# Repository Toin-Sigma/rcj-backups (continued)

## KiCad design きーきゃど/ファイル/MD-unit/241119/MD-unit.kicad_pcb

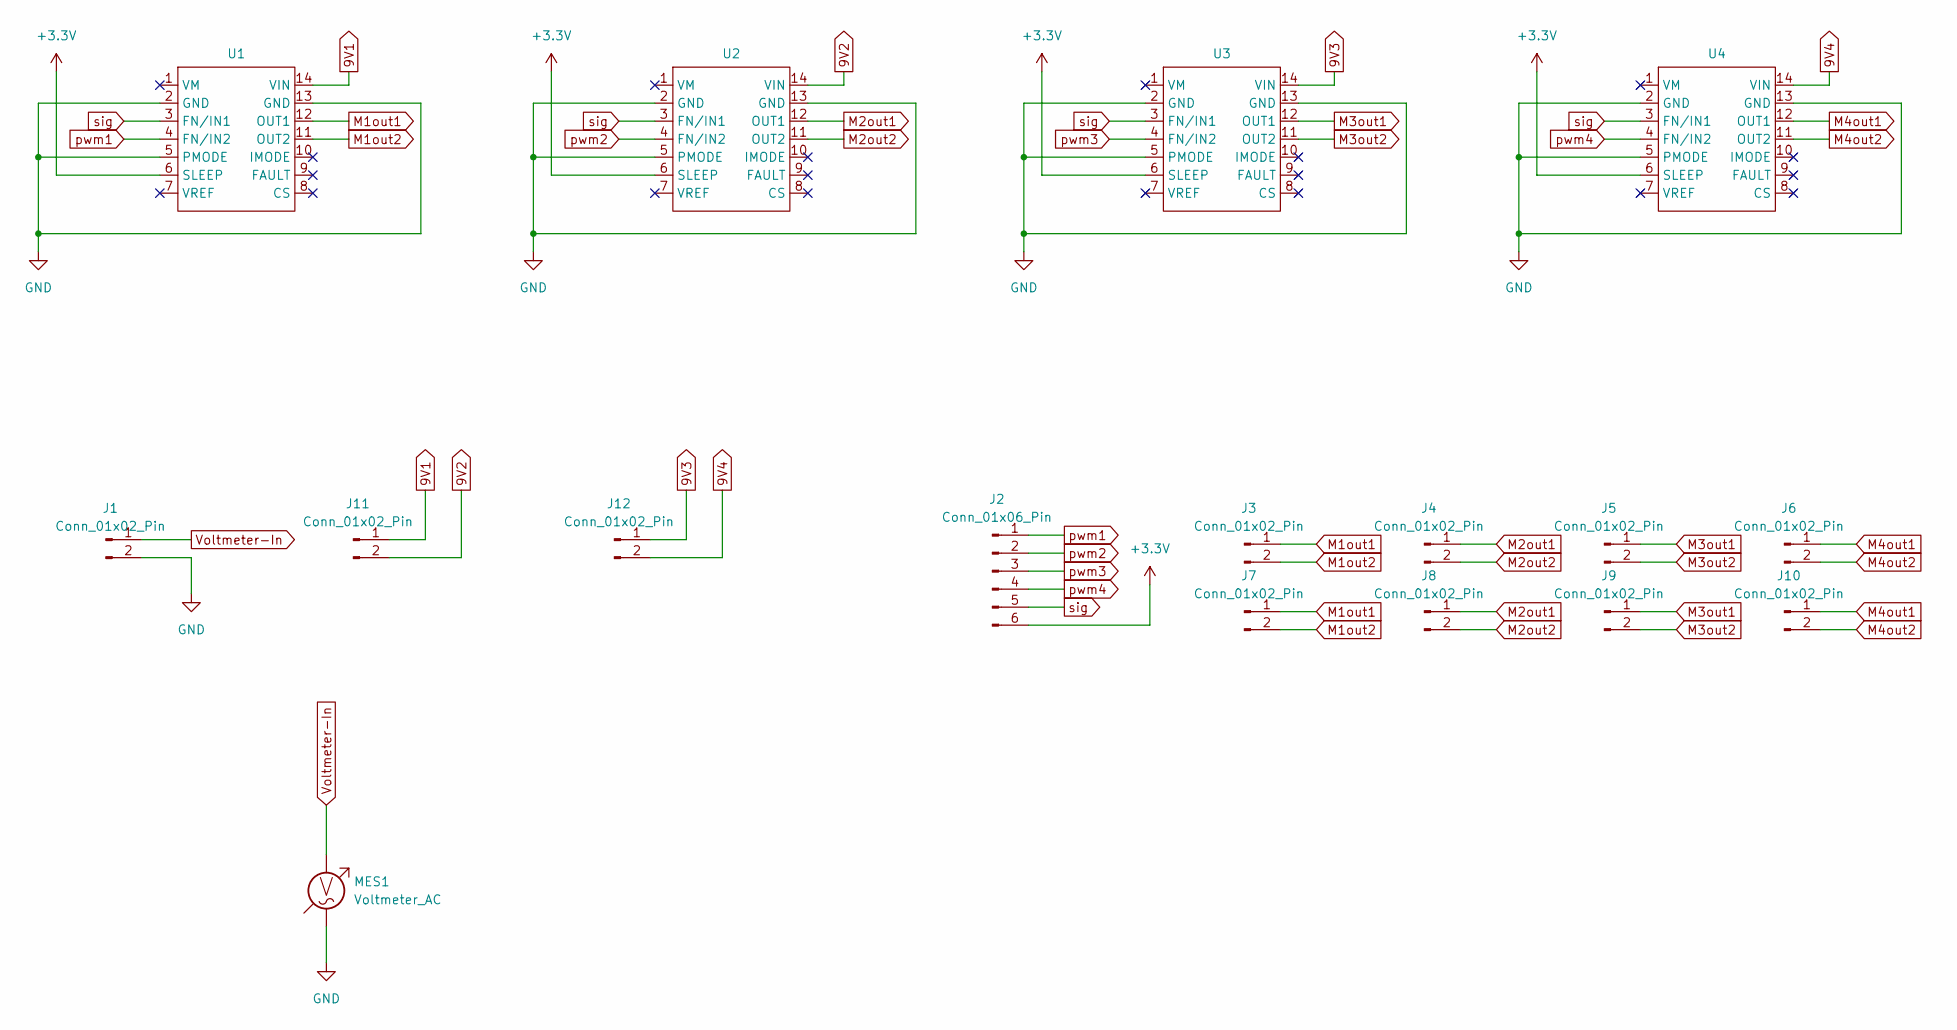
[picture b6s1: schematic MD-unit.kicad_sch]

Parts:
J1, J3, J4, J5, J6, J11, J12: Conn_01x02_Pin; AMASS_XT30U-M_1x02_P5.0mm_Vertical
J2: Conn_01x06_Pin; JST_XH_B6B-XH-A_1x06_P2.50mm_Vertical
J7, J8, J9, J10: Conn_01x02_Pin; JST_XH_B2B-XH-A_1x02_P2.50mm_Vertical
MES1: Voltmeter_AC; VoltMeter
U1, U2, U3, U4: DRV8874

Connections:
9V1: J11.1, U1.14 (VIN)
9V2: J11.2, U2.14 (VIN)
9V3: J12.1, U3.14 (VIN)
9V4: J12.2, U4.14 (VIN)
+3.3V: J2.6, U1.6 (SLEEP), U2.6 (SLEEP), U3.6 (SLEEP), U4.6 (SLEEP)
GND: J1.2, MES1.1, U1.2 (GND), U1.5 (PMODE), U1.13 (GND), U2.2 (GND), U2.5 (PMODE), U2.13 (GND), U3.2 (GND), U3.5 (PMODE), U3.13 (GND), U4.2 (GND), U4.5 (PMODE), U4.13 (GND)
M1out1: J3.1, J7.1, U1.12 (OUT1)
M1out2: J3.2, J7.2, U1.11 (OUT2)
M2out1: J4.1, J8.1, U2.12 (OUT1)
M2out2: J4.2, J8.2, U2.11 (OUT2)
M3out1: J5.1, J9.1, U3.12 (OUT1)
M3out2: J5.2, J9.2, U3.11 (OUT2)
M4out1: J6.1, J10.1, U4.12 (OUT1)
M4out2: J6.2, J10.2, U4.11 (OUT2)
Voltmeter-In: J1.1, MES1.2
pwm1: J2.1, U1.4 (FN/IN2)
pwm2: J2.2, U2.4 (FN/IN2)
pwm3: J2.3, U3.4 (FN/IN2)
pwm4: J2.4, U4.4 (FN/IN2)
sig: J2.5, U1.3 (FN/IN1), U2.3 (FN/IN1), U3.3 (FN/IN1), U4.3 (FN/IN1)

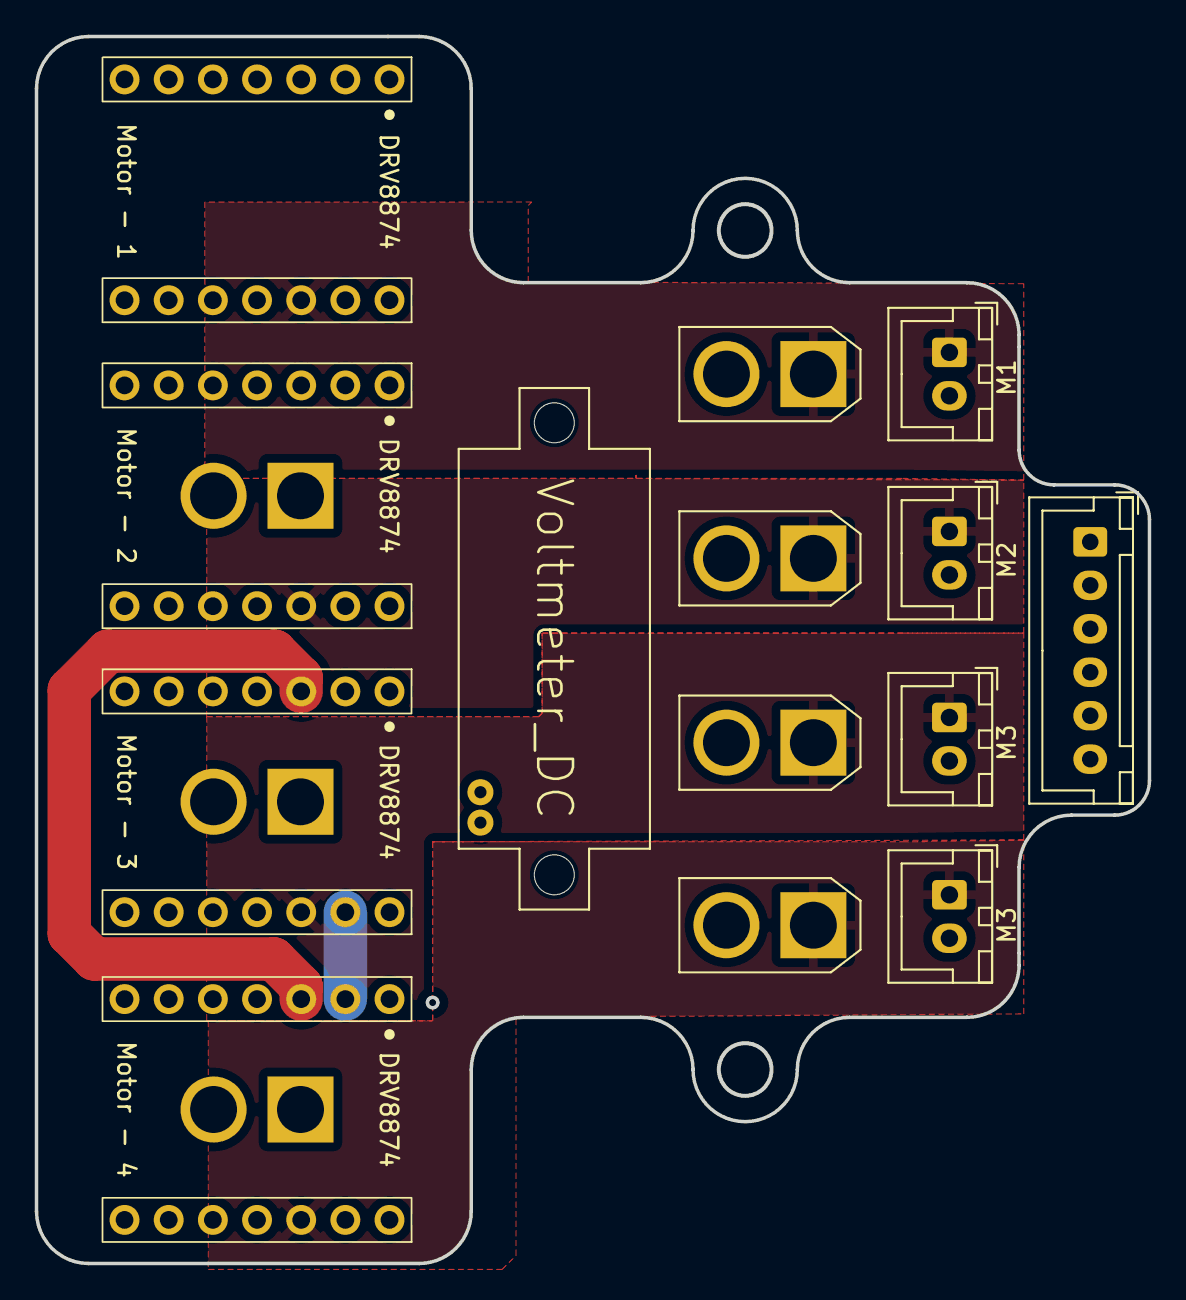
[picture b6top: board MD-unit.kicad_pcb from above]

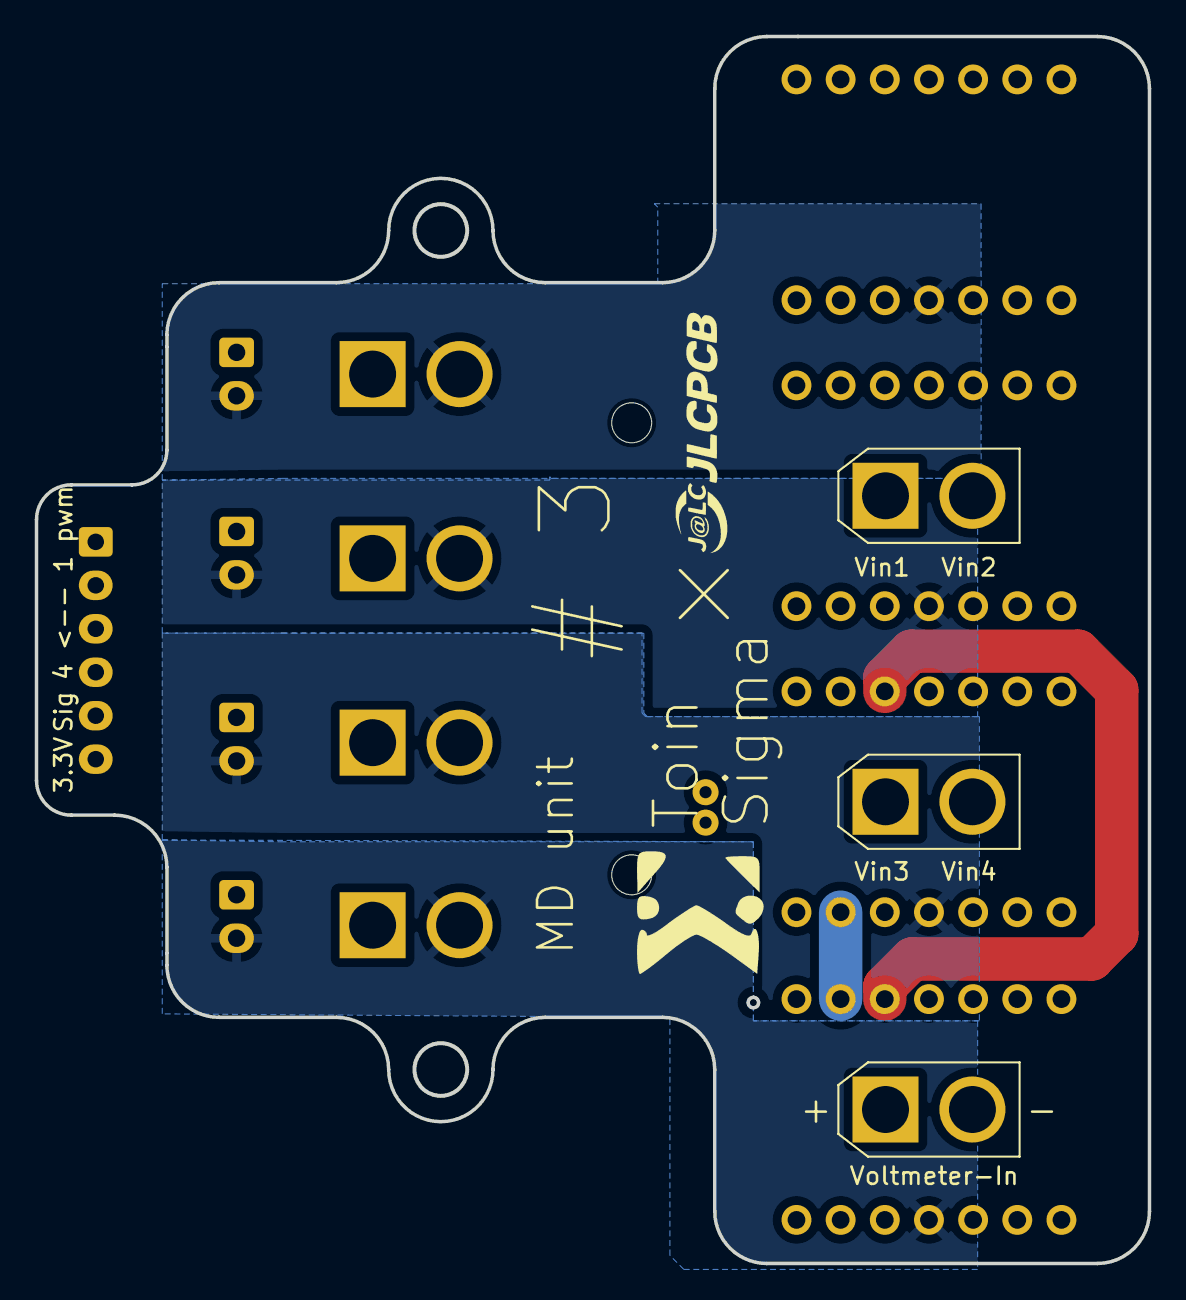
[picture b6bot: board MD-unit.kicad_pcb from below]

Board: 4 copper layers, 64.0 x 70.6 mm, 17 parts (3 on the bottom side), 20 nets.

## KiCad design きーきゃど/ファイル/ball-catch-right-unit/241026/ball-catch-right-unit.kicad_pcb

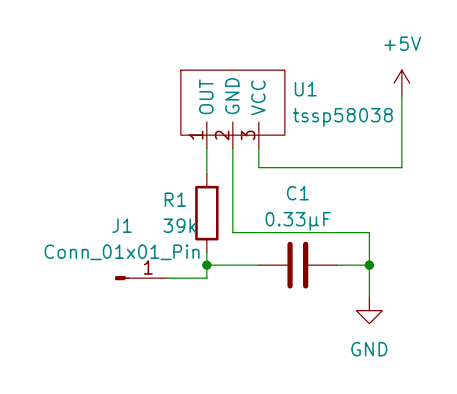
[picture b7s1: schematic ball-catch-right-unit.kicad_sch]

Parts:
C1: 0.33μF; C_0603_1608Metric_Pad1.08x0.95mm_HandSolder
J1: Conn_01x01_Pin; 1-pin
R1: 39k; R_0603_1608Metric_Pad0.98x0.95mm_HandSolder
U1: tssp58038

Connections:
+5V: U1.3 (VCC)
GND: C1.2, U1.2 (GND)
unnamed: C1.1, J1.1, R1.1
unnamed: R1.2, U1.1 (OUT)

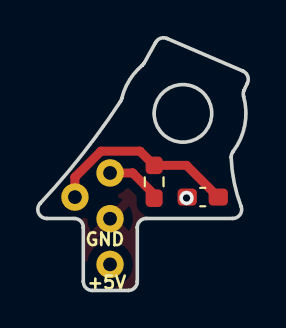
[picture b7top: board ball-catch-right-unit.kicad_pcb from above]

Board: 2 copper layers, 11.7 x 14.0 mm, 4 parts (0 on the bottom side), 3 nets.

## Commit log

2024-10-26 Create UPs!!!
2024-11-19 Create ups!
2024-11-19 Create ups
2024-11-19 Create ups!!
2024-12-27 Create backups
2025-01-15 Create backups!!!
